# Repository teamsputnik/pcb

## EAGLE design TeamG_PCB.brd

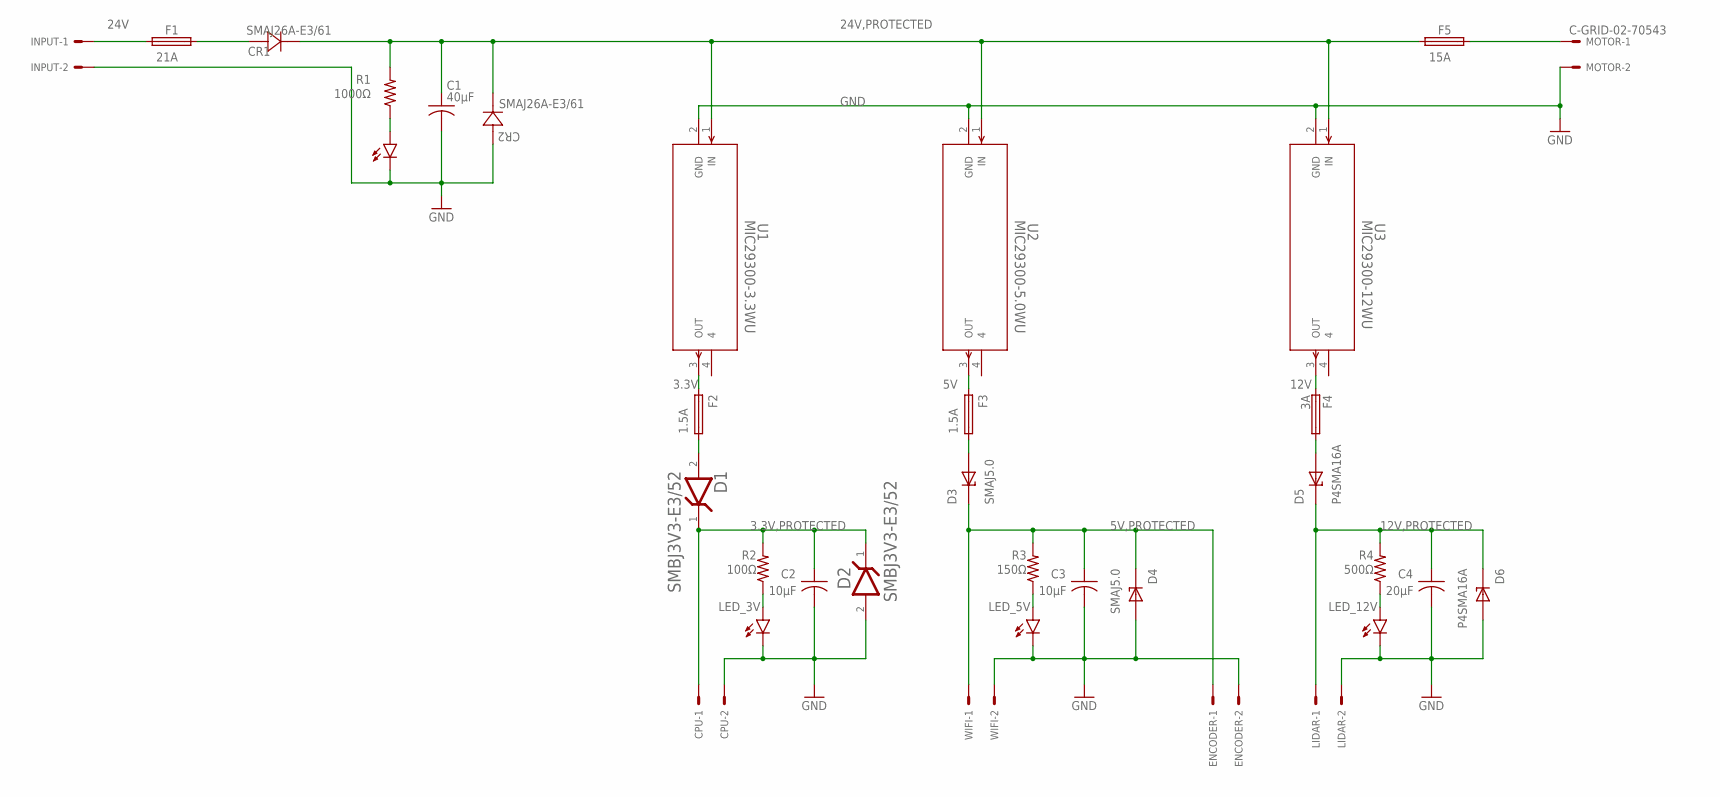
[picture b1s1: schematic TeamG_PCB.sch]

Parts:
24VLED: 0; 1206
C1: 40µF; C1210
C2, C3: 10µF; C1210
C4: 20µF; C1210
CPU: C-GRID-02-70543; 70543-02
CR1, CR2: SMAJ26A-E3/61; DIODE_DO-214AC
D1, D2: VISHAY_SMBJ3V3-E3-52VISHAY_SMBJ3V3-E3-52_0_0; VISHAY_SMBJ3V3-E3-52_0
D3, D4: SMAJ5.0; DIOM4325X250N
D5, D6: P4SMA16A; DIOM4325X250N
ENCODER: C-GRID-02-70543; 70543-02
F1: 21A; TE5
F2, F3: 1.5A; TE5
F4: 3A; TE5
F5: 15A; TE5
INPUT: 5566-2
LED_3V, LED_5V, LED_12V: 0; 1206
LIDAR: C-GRID-02-70543; 70543-02
MOTOR: C-GRID-02-70543; 70543-02
R1: 1000Ω; R1206
R2: 100Ω; R1206
R3: 150Ω; R1206
R4: 500Ω; R1206
U1: MIC29300-3.3WU; TO-263-3_MCL
U2: MIC29300-5.0WU; TO-263-3_MCL
U3: MIC29300-12WU; TO-263-3_MCL
WIFI: C-GRID-02-70543; 70543-02

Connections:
3.3V: F2.2, U1.3 (OUT)
3.3V,PROTECTED: C2.1, CPU.1, D1.1 (CATHODE), D2.1 (CATHODE), R2.2
5V: F3.2, U2.3 (OUT)
5V,PROTECTED: C3.1, D3.C, D4.C, ENCODER.1, R3.2, WIFI.1
12V: F4.2, U3.3 (OUT)
12V,PROTECTED: C4.1, D5.C, D6.C, LIDAR.1, R4.2
24V: F1.1, INPUT.1
24V,PROTECTED: C1.1, CR1.1, CR2.1, F5.1, R1.2, U1.1 (IN), U2.1 (IN), U3.1 (IN)
GND: 24VLED.C, C1.2, C2.2, C3.2, C4.2, CPU.2, CR2.2, D2.2 (ANODE), D4.A, D6.A, ENCODER.2, INPUT.2, LED_3V.C, LED_5V.C, LED_12V.C, LIDAR.2, MOTOR.2, U1.2 (GND), U2.2 (GND), U3.2 (GND), WIFI.2
MOTOR_24V: F5.2, MOTOR.1
unnamed: D1.2 (ANODE), F2.1
unnamed: CR1.2, F1.2
unnamed: LED_12V.A, R4.1
unnamed: D5.A, F4.1
unnamed: 24VLED.A, R1.1
unnamed: LED_3V.A, R2.1
unnamed: LED_5V.A, R3.1
unnamed: D3.A, F3.1

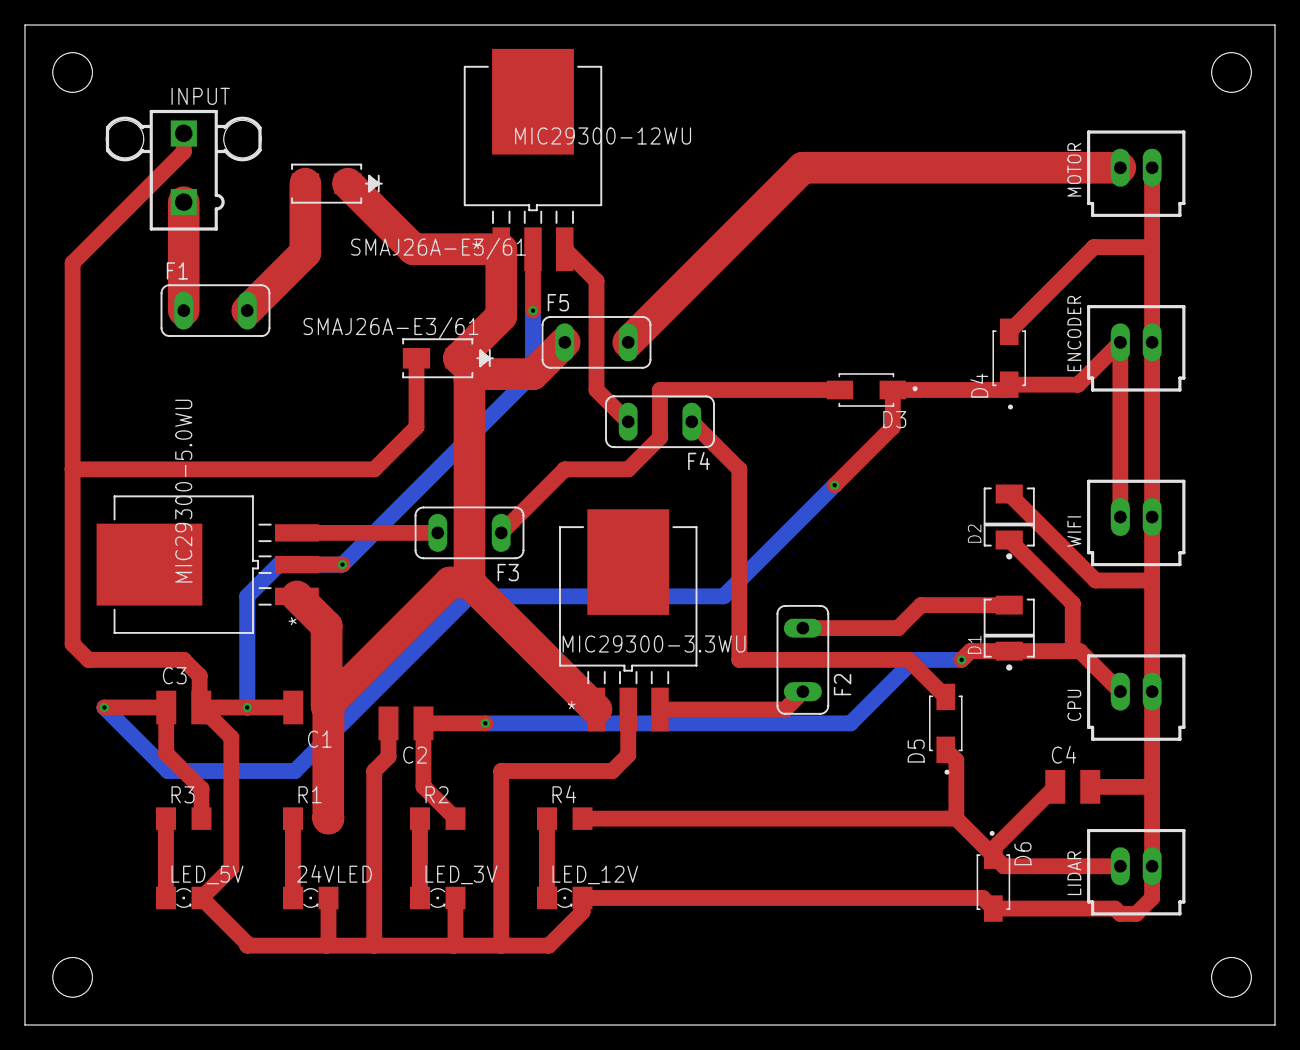
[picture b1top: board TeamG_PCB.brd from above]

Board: 2 copper layers, 100.0 x 80.0 mm, 34 parts (0 on the bottom side), 18 nets.

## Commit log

2024-02-14 Add libraries
2024-02-15 Add new PCB

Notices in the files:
parts and their libraries:
COPYRIGHT: Copyright (C) 2022 Ultra Librarian. All rights reserved.
